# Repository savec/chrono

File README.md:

# chrono
On-barrel chronograph with android integration

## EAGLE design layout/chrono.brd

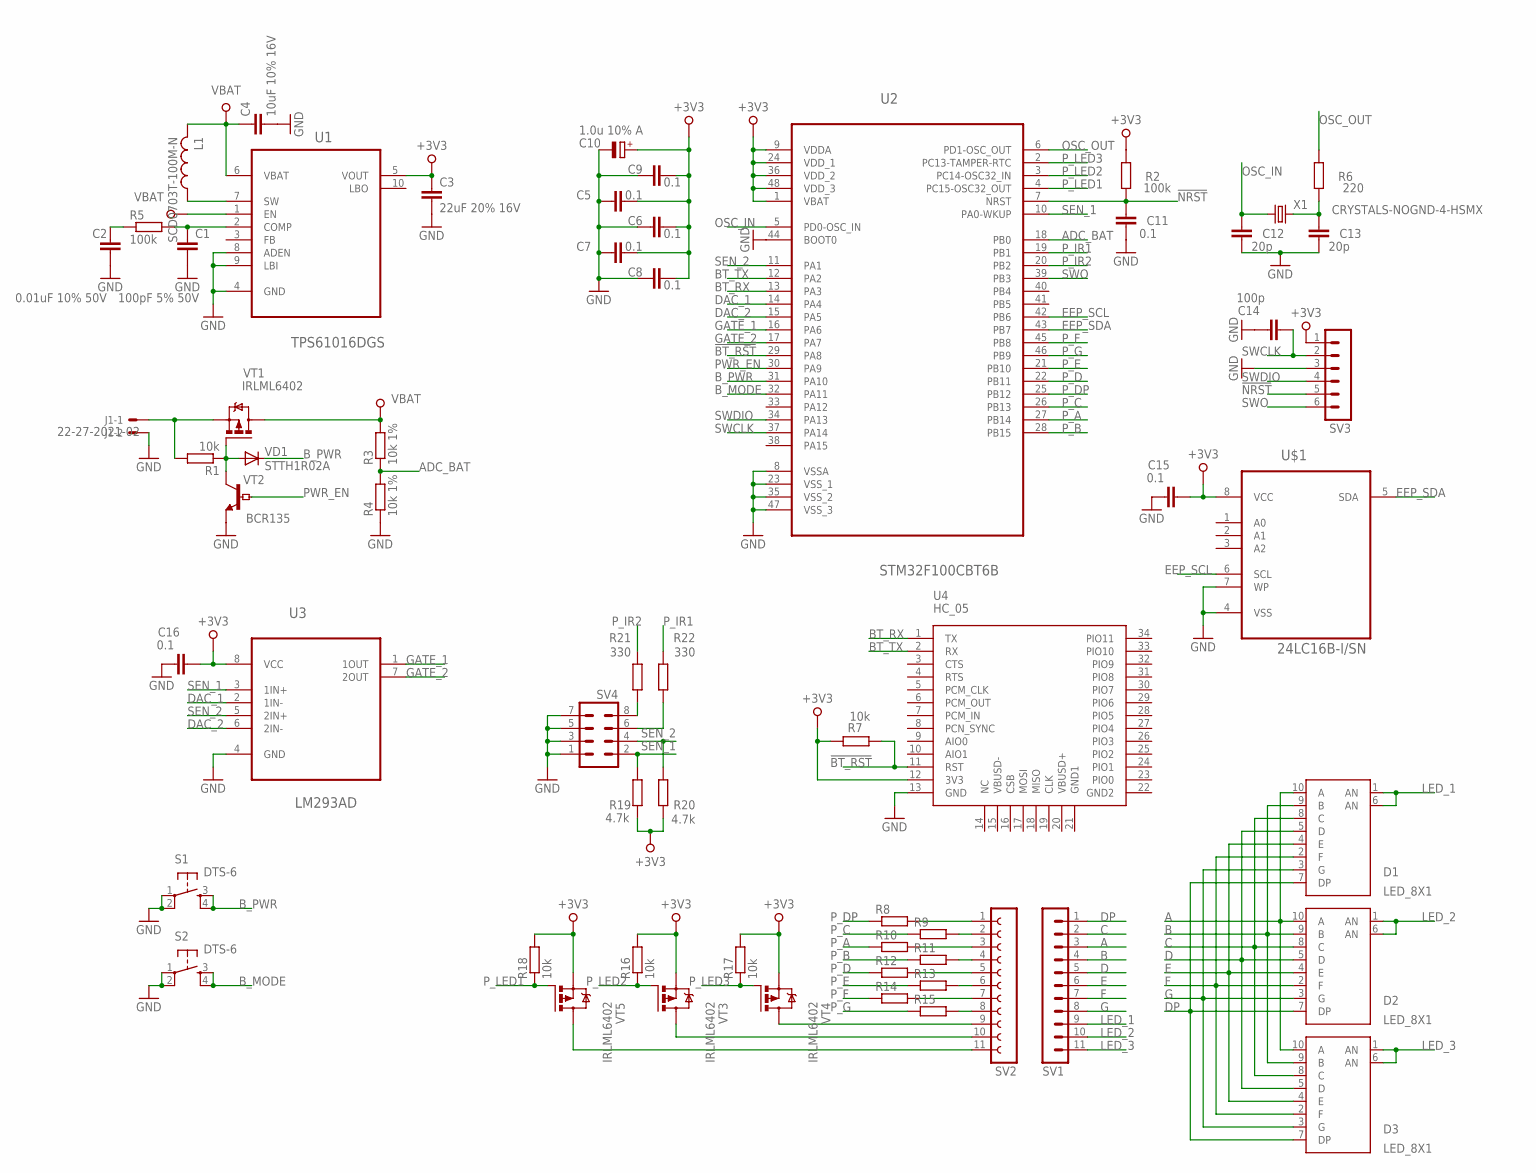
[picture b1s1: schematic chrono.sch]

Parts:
C1: 100pF 5% 50V; C0805
C2: 0.01uF 10% 50V; C0805
C3: 22uF 20% 16V; C1206
C4: 10uF 10% 16V; C0805
C5, C6, C7, C8, C9, C11, C15, C16: 0.1; C0603
C10: 1.0u 10% A; SMC_A
C12, C13: 20p; C0603
C14: 100p; C0603
D1, D2, D3: LED_8X1; LED_DIP10
J1: 22-27-2021-02; 6410-02
L1: SCD0703T-100M-N; SCD0703
R1: 10k; R0805
R2: 100k; R0603
R3, R4: 10k 1%; R0603
R5: 100k; R0805
R6: 220; R0603
R7, R16, R17, R18: 10k; R0603
R8, R9, R10, R11, R12, R13, R14, R15: R-EU_R0603; R0603
R19, R20: 4.7k; R0603
R21, R22: 330; R0603
S1, S2: DTS-6
SV1: MA11-1W
SV2: FE11-1; FE11
SV3: MA06-1
SV4: MA04-2
U1: TPS61016DGS; SOP50P490X110-10N
U2: STM32F100CBT6B; QFP50P900X900X160-48N
U3: LM293AD; SOIC127P600X175-8N
U4: HC_05; BLUETOOTH_SMD
U$1: 24LC16B-I/SN; SOIC127P600X175-8N
VD1: STTH1R02A; SMA
VT1, VT3, VT4, VT5: IRLML6402; MICRO3
VT2: BCR135; SOT23-BEC
X1: CRYSTALS-NOGND-4-HSMX; HC49-4-HSMX

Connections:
!BT_RST: R7.2, U2.29 (PA8), U4.11 (RST)
!NRST: C11.1, R2.2, SV3.5, U2.7 (NRST)
+3V3: C3.1, C5.2, C6.2, C7.2, C8.2, C9.1, C10.+, C15.2, C16.2, R2.1, R7.1, R16.2, R17.2, R18.2, R19.1, R20.1, SV3.1, U1.5 (VOUT), U2.1 (VBAT), U2.9 (VDDA), U2.24 (VDD_1), U2.36 (VDD_2), U2.48 (VDD_3), U3.8 (VCC), U4.12 (3V3), U$1.8 (VCC), VT3.2 (S), VT4.2 (S), VT5.2 (S)
A: D1.10 (A), D2.10 (A), D3.10 (A), SV1.3
ADC_BAT: R3.1, R4.2, U2.18 (PB0)
B: D1.9 (B), D2.9 (B), D3.9 (B), SV1.4
BT_RX: U2.13 (PA3), U4.1 (TX)
BT_TX: U2.12 (PA2), U4.2 (RX)
B_MODE: S2.3, S2.4, U2.32 (PA11)
B_PWR: S1.3, S1.4, U2.31 (PA10), VD1.C
C: D1.8 (C), D2.8 (C), D3.8 (C), SV1.2
D: D1.5 (D), D2.5 (D), D3.5 (D), SV1.5
DAC_1: U2.14 (PA4), U3.2 (1IN-)
DAC_2: U2.15 (PA5), U3.6 (2IN-)
DP: D1.7 (DP), D2.7 (DP), D3.7 (DP), SV1.1
E: D1.4 (E), D2.4 (E), D3.4 (E), SV1.6
EEP_SCL: U2.42 (PB6), U$1.6 (SCL)
EEP_SDA: U2.43 (PB7), U$1.5 (SDA)
F: D1.2 (F), D2.2 (F), D3.2 (F), SV1.7
G: D1.3 (G), D2.3 (G), D3.3 (G), SV1.8
GATE_1: U2.16 (PA6), U3.1 (1OUT)
GATE_2: U2.17 (PA7), U3.7 (2OUT)
GND: C1.2, C2.2, C3.2, C4.2, C5.1, C6.1, C7.1, C8.1, C9.2, C10.-, C11.2, C12.2, C13.2, C14.1, C15.1, C16.1, J1.2, R4.1, S1.1, S1.2, S2.1, S2.2, SV3.3, SV4.1, SV4.3, SV4.5, SV4.7, U1.4 (GND), U1.8 (ADEN), U1.9 (LBI), U2.8 (VSSA), U2.23 (VSS_1), U2.35 (VSS_2), U2.44 (BOOT0), U2.47 (VSS_3), U3.4 (GND), U4.13 (GND), U$1.4 (VSS), U$1.7 (WP), VT2.E
LED_1: D1.1 (AN), D1.6 (AN), SV1.9
LED_2: D2.1 (AN), D2.6 (AN), SV1.10
LED_3: D3.1 (AN), D3.6 (AN), SV1.11
unnamed: J1.1, R1.2, VT1.2 (S)
unnamed: R1.1, VD1.A, VT1.1 (G), VT2.C
unnamed: C1.1, R5.2, U1.2 (COMP)
unnamed: L1.P$1 (1), U1.7 (SW)
unnamed: C2.1, R5.1
unnamed: C13.1, R6.2, X1.2
unnamed: R8.2, SV2.1
unnamed: R9.2, SV2.2
unnamed: R10.2, SV2.3
unnamed: R11.2, SV2.4
unnamed: R21.1, SV4.8
unnamed: R12.2, SV2.5
unnamed: R13.2, SV2.6
unnamed: R14.2, SV2.7
unnamed: R15.2, SV2.8
unnamed: SV2.9, VT4.3 (D)
unnamed: SV2.10, VT3.3 (D)
unnamed: SV2.11, VT5.3 (D)
unnamed: R22.1, SV4.6
OSC_IN: C12.1, U2.5 (PD0-OSC_IN), X1.1
OSC_OUT: R6.1, U2.6 (PD1-OSC_OUT)
PWR_EN: U2.30 (PA9), VT2.B
P_A: R10.1, U2.27 (PB14)
P_B: R11.1, U2.28 (PB15)
P_C: R9.1, U2.26 (PB13)
P_D: R12.1, U2.22 (PB11)
P_DP: R8.1, U2.25 (PB12)
P_E: R13.1, U2.21 (PB10)
P_F: R14.1, U2.45 (PB8)
P_G: R15.1, U2.46 (PB9)
P_IR1: R22.2, U2.19 (PB1)
P_IR2: R21.2, U2.20 (PB2)
P_LED1: R18.1, U2.4 (PC15-OSC32_OUT), VT5.1 (G)
P_LED2: R16.1, U2.3 (PC14-OSC32_IN), VT3.1 (G)
P_LED3: R17.1, U2.2 (PC13-TAMPER-RTC), VT4.1 (G)
SEN_1: R19.2, SV4.2, U2.10 (PA0-WKUP), U3.3 (1IN+)
SEN_2: R20.2, SV4.4, U2.11 (PA1), U3.5 (2IN+)
SWCLK: C14.2, SV3.2, U2.37 (PA14)
SWDIO: SV3.4, U2.34 (PA13)
SWO: SV3.6, U2.39 (PB3)
VBAT: C4.1, L1.P$2 (2), R3.2, U1.1 (EN), U1.6 (VBAT), VT1.3 (D)

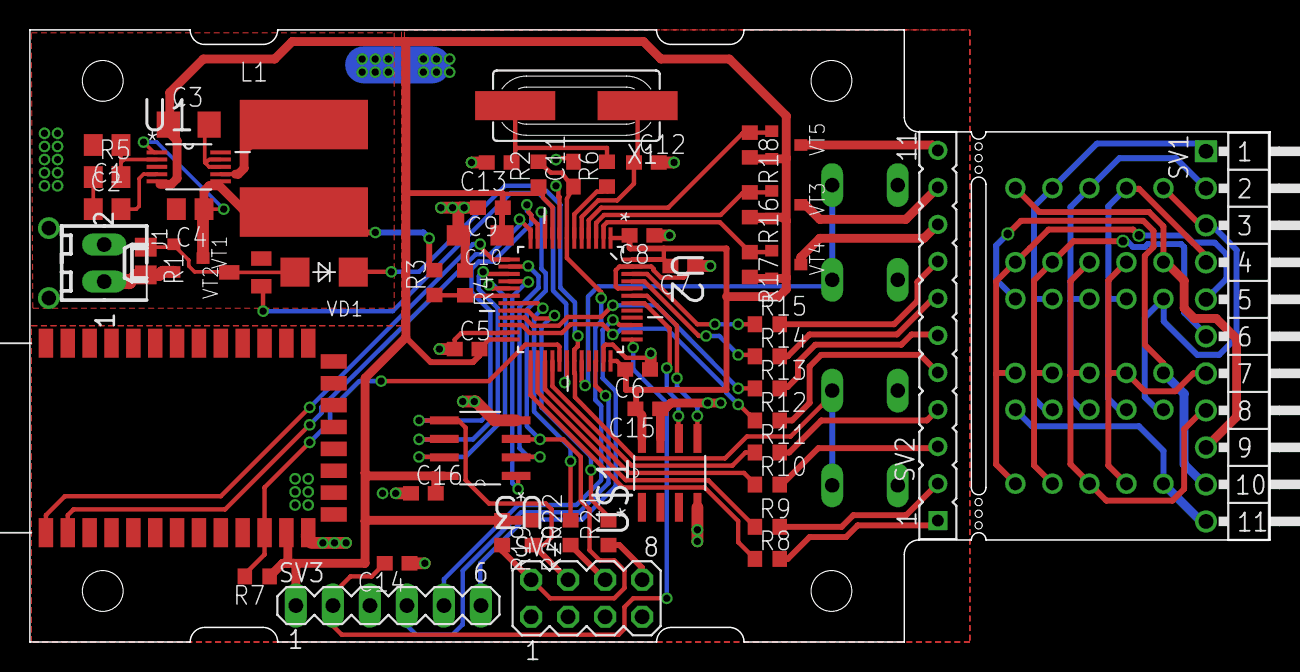
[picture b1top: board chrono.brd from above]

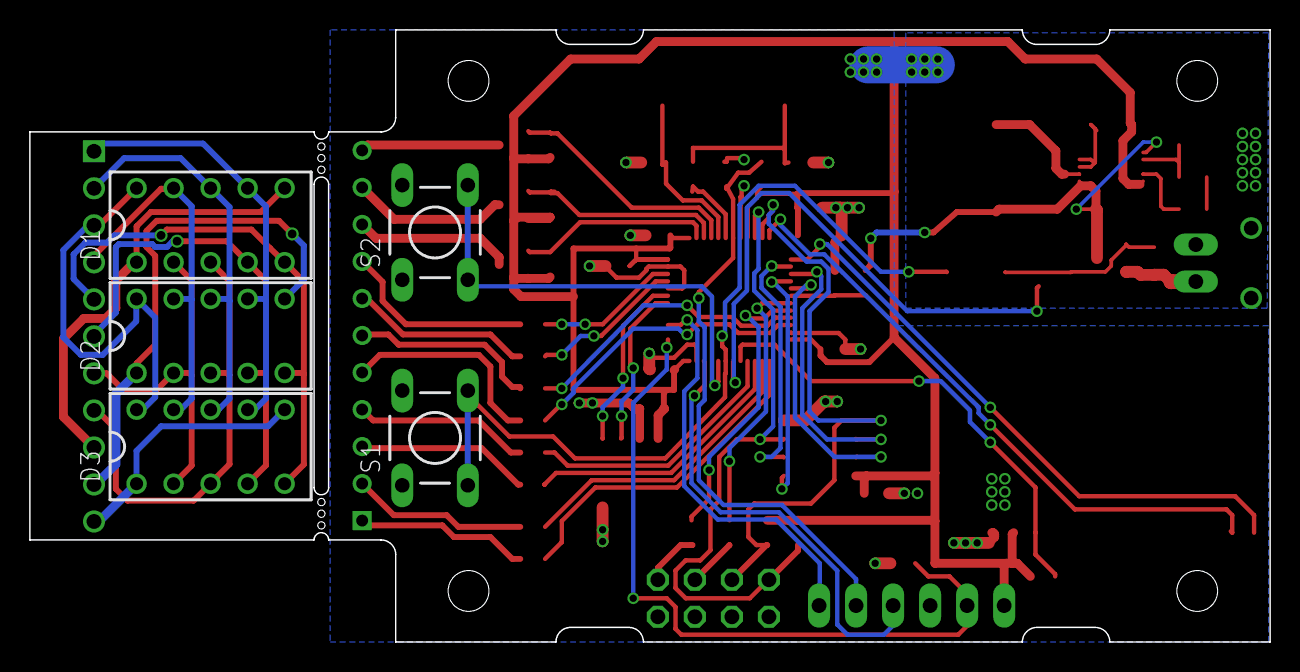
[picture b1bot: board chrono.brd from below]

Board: 2 copper layers, 85.1 x 42.0 mm, 61 parts (5 on the bottom side), 67 nets.

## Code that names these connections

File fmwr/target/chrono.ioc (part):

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Mcu.Name=STM32F100C(8-B)Tx
Mcu.Package=LQFP48
Mcu.UserName=STM32F100CBTx
PA0-WKUP.Signal=ADCx_IN0
PA1.Signal=ADCx_IN1
PA11.Signal=GPIO_Input
PA13.Mode=Trace_Asynchronous_SW
PA13.Signal=SYS_JTMS-SWDIO
PA14.Mode=Trace_Asynchronous_SW
PA14.Signal=SYS_JTCK-SWCLK
PA4.Signal=COMP_DAC1_group
PA5.Signal=COMP_DAC2_group
PA6.GPIOParameters=GPIO_PuPd,GPIO_ModeDefaultEXTI
PA6.GPIO_ModeDefaultEXTI=GPIO_MODE_IT_RISING
PA6.GPIO_PuPd=GPIO_PULLUP
PA6.Signal=GPXTI6
PA7.GPIOParameters=GPIO_PuPd,GPIO_ModeDefaultEXTI
PA7.GPIO_ModeDefaultEXTI=GPIO_MODE_IT_RISING
PA7.GPIO_PuPd=GPIO_PULLUP
PA7.Signal=GPXTI7
PB0.Signal=ADCx_IN8
PB1.Signal=GPIO_Output
PB10.Signal=GPIO_Output
PB11.Signal=GPIO_Output
PB12.Signal=GPIO_Output
PB13.Signal=GPIO_Output
PB14.Signal=GPIO_Output
PB15.Signal=GPIO_Output
PB2.Signal=GPIO_Output
PB3.Mode=Trace_Asynchronous_SW
PB3.Signal=SYS_JTDO-TRACESWO
PB6.Mode=I2C
PB6.Signal=I2C1_SCL
PB7.Mode=I2C
PB7.Signal=I2C1_SDA
PB8.Signal=GPIO_Output
PB9.Signal=GPIO_Output
PC13-TAMPER-RTC.Signal=GPIO_Output
PC14-OSC32_IN.Signal=GPIO_Output
PC15-OSC32_OUT.Signal=GPIO_Output
PD0-OSC_IN.Mode=HSE-External-Oscillator
PD0-OSC_IN.Signal=RCC_OSC_IN
PD1-OSC_OUT.Mode=HSE-External-Oscillator
PD1-OSC_OUT.Signal=RCC_OSC_OUT
RCC.SYSCLKFreq_VALUE=8000000
RCC.SYSCLKSource=RCC_SYSCLKSOURCE_HSE
board=custom

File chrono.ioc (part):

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Mcu.Name=STM32F100C(8-B)Tx
Mcu.Package=LQFP48
Mcu.UserName=STM32F100CBTx
PA0-WKUP.Signal=ADCx_IN0
PA1.Signal=ADCx_IN1
PA11.Signal=GPIO_Input
PA13.Mode=Trace_Asynchronous_SW
PA13.Signal=SYS_JTMS-SWDIO
PA14.Mode=Trace_Asynchronous_SW
PA14.Signal=SYS_JTCK-SWCLK
PA2.Mode=Asynchronous
PA2.Signal=USART2_TX
PA3.Mode=Asynchronous
PA3.Signal=USART2_RX
PA4.Signal=COMP_DAC1_group
PA5.Signal=COMP_DAC2_group
PA6.Signal=GPXTI6
PA7.Signal=GPXTI7
PB0.Signal=ADCx_IN8
PB3.Mode=Trace_Asynchronous_SW
PB3.Signal=SYS_JTDO-TRACESWO
PB6.Mode=I2C
PB6.Signal=I2C1_SCL
PB7.Mode=I2C
PB7.Signal=I2C1_SDA
PC13-TAMPER-RTC.Signal=GPIO_Output
PC14-OSC32_IN.Signal=GPIO_Output
PC15-OSC32_OUT.Signal=GPIO_Output
PD0-OSC_IN.Signal=RCC_OSC_IN
PD1-OSC_OUT.Signal=RCC_OSC_OUT

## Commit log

2015-11-27 schem in progress
2015-11-27 test
2015-12-02 routing
2015-12-12 routing finished
2015-12-19 discovery board prototype started
2015-12-19 lcd test
2015-12-19 some periph
2015-12-19 PC13
2015-12-24 adc, median filter
2015-12-25 dac, median filter corrected
2015-12-26 median filter again
2015-12-26 uart dma
2015-12-26 send_data fix
2018-08-10 export all to local library
2019-03-02 cube-mx generated template
2019-03-02 .gitignore
2019-03-02 added cpp support
2019-03-02 Updated makefile; added ported memory allocators
2019-03-03 added wrapper for tasks
2019-03-09 Added Indixator class implementation
2019-03-10 Added ADC class
2019-03-16 Updated: all low level initializations called before static constructors.
2019-03-16 Updated ADC class; added MedianFilter class
2019-03-16 Updated heap size; cleanup
2019-03-23 Updated using of Indicator & ADC classes as singleton; Using task notify instead of event groups; Task notifications moved to ActiveObject base class
2019-03-24 Added IR diodes on
2019-03-24 Added cDAC class; Renamed ADC & Idicator classes
2019-03-24 Enabled external interrupts
2019-03-30 Added autoadjusting of comparators reference
2019-03-30 Added exti handlers
2019-03-30 Added Chrono object isr notifying
2019-03-30 Added speed measuring
